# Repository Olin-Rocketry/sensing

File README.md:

# Sensing

Repository for all Olin Rocketry hardware and firmware.

The purpose of the avionics system is to determine when to deploy the drogue and main chutes, and to send the signal to do so to the recovery system. The flight computer contains several sensors to help detect apogee, and a microcontroller to read and process the data and send the signal.

The avionics system consists of

- a commercial-off-the-shelf (COTS) flight computer;
- a student-designed flight computer, which includes sensors, microcontroller, GPS, and radio; and
- a student-designed battery management system (BMS).

The COTS computer is a **\_** model. It has its own batteries, sensors, and radio and can trigger the recovery system independently. It is intended as a backup and is required by IREC competition rules (partly so they have a reliable altitude measurement for the competition). The BMS is described on the Power Management subteam page. It can suppy a steady 3.3V current up to about 1000 mA to the student-designed flight computer board.

**The flight computer consists of a Teensy 3.6 microcontroller and various sensors.**

- The [Teensy 3.6](https://www.pjrc.com/teensy/card9a_rev1.pdf) is computationally powerful enough for complex data processing, has many interrupt pins, and many pins in general for connecting multiple sensors. It also has a built-in SD card reader. The decision to use it was made before the Fall 2020 semester; other options were considered and may be viable for future iterations. The main drawback of the Teensy 3.6 is its cost, at around $30. This makes having multiple prototypes very expensive, especially if we want to distribute copies to team members living in separate places.
- We considered 3 different inertial measurement units (IMUs, or accelerometers):
  - [ADXL345](https://www.analog.com/media/en/technical-documentation/data-sheets/ADXL345.pdf) is a very common 3-axis accelerometer. It is widely available and was already in stock from JLC, the company manufacturing our board. This means our boards will have the ADXL345 already populated when it is shipped to us, a bonus.
  - [BMI088](https://download.mikroe.com/documents/datasheets/BMI088_Datasheet.pdf) is a 6-axis accelerometer and gyroscope (axes 4-6 are angular acceleration).
  - [BNO055](https://cdn-shop.adafruit.com/datasheets/BST_BNO055_DS000_12.pdf) is a 9-axis accelerometer, relative, and absolute gyroscope (axes 7-9 are absolute orientation).

We designed our Rev1 PCB to hold all three IMUs, so that we could test all of them at once. However, as of ordering time in January, the BMI088 and BNO055 were out of stock at Digikey and Mouser, so these were never tested.

- [MPL3115A2](https://www.nxp.com/docs/en/data-sheet/MPL3115A2.pdf) is a barometer calibrated to provide altimetry. It is the most important sensor, as it allows us to determine our absolute altitude. Our simplest apogee detection is triggered by a certain number of consecutive decreasing altitude measurements.
- Header pins for the [Adafruit Ultimate GPS Breakout (Version 3)](https://www.adafruit.com/product/746?__hstc), a $40 complete GPS module.
- Header pins for the [RFM9X LoRa Packet Radio Breakout](https://learn.adafruit.com/adafruit-rfm69hcw-and-rfm96-rfm95-rfm98-lora-packet-padio-breakouts/arduino-wiring), the currenty preferred radio (see Communications subteam page).

**Rev 1 Testing Update: Spring 2021**

The sensors on Rev1 (the ADXL345 accelerometer and the MPL3115A2 barometer) work, and the data can be read over I2C. The current data format is a csv file with time since launch, x, y, and z acceleration, pressure, altitude, and temperature. The readings from the accelerometer have very little noise when at rest (the only test performed so far - others to follow soon). The barometer has some issues. First of all, it has an offset of about 1.7 atmospheres. When those 1.7 atm are subtracted out, however, it provides high precision and sensitivity. The altitude readings are off by the same offset, as I believe they are calculated from the barometer reading anyway. The temperature has some 20 degrees F offset and significant drift of 2-5 degrees F over a few minutes. More testing to follow.

I looked at the specs and realized that the ADXL345 and MPL3115A2 together consume less than 3 mA of current at their max. Since the Teensy can output 250 mA through those pins, I don’t see why to use an external power source; we can just use the 3.3V pins on the Teensy.
The tests I have done have been using the 3.3V pin as a power source.

**Tests performed 3/26/2021:**

**Power supply test:** Get an external power supply and give 3.3V to the power inputs. Test the test points and the Teensy’s Vin pin. Test data logging onto SD card. Test sensors connected only to external power supply vs. connected to Teensy 3.3V pin vs. connected to both.

**Results:**
The transistor part of the Rev1 power management circuit did not work. For some reason, there was always only ~0.6V on both the gate and drain pins, and so 0.6V on the rest of the PCB. I tried several pin configurations and nothing helped. It worked fine when I bypassed the transistor and powered 3.3V to both the Teensy and the PCB.
The Teensy could not write to the SD card when the PCB and Teensy were powered independently; it only works when the rest of the PCB is powered through the Teensy’s dedicated 3.3V pin. Therefore, I recommend just using the Teensy’s 3.3V pin to power the sensors.

In this case, I suggest the voltage supplied by the BMS should be 3.6V instead of 3.3V, so that the linear voltage regulator on the Teensy can effectively supply the 3.3V to the sensors. Voltage regulators necessariy have a small voltage drop across them, although I came across a [source](https://forum.pjrc.com/threads/55789-Power-Teensy-3-6-with-lipo-battery?p=203568&viewfull=1#post203568) that says the Teensy will bypass its voltage regulator if the voltage is too low, so there is not necessarily an issue.

**MPL3115A2 Accuracy Test:** Take the Rev1 board up and down the stairs of the MAC building 2 times and measure altitude difference.

**Results:**
The readings are inaccurate, yet very precise. The pressure has reads on the order of 200 kPa, which is double what is expected (1 atmosphere is about 100 kPa), and the temperature reads 90 degrees F in a 70 degree room. Yet after the offset is subtracted, the sensor tracks changes in height of less than 20 feet (the distance between floors in the MAC, and the highest resolution analyzed) quite well. The graph below shows the corrected elevation and temperature over the course of my trip up and down the stairs of the MAC, then outside onto the great lawn and up to the 4th floor of West Hall. There is some drift over time as it sat on my desk after “landing,” on the order of 20 feet over 20 minutes. This is worrying, but it will likely not be a problem during a launch lasting a few minutes.

**Developing the Rev 2 board**

With the ADXL345 and MPL3115A2 sensors confirmed to work, the main objective of the Rev 2 board is to make it fit into the avionics bay. The final board is 80mm tall by 72mm wide and has a mounting hole in each corner. The power supply transistor circuit has been replaced with a power multiplexer, a zener diode was added for overvoltage protection, and the power from the BMS goes directly into the Vin pin on the Teensy; the sensors and other circuitry are powered by the Teensy's 3.3V pin as discussed above. Additionally, 5 debugging LEDs, one power LED, and a [buzzer](https://www.digikey.com/en/products/detail/mallory-sonalert-products-inc/PT-1340P-P10-PQ/4996070) have also been added and are controlled by spare digital pins on the Teensy. A 10uF capacitor was added between the power and ground pins of the radio upon testing by the Communications team.

The board has been ordered from JLC and will arrive within a couple days.

## Guide to creating PCBs

**The process for creating the flight computer PCB has multiple stages:**
  1. Components are selected, including the microcontroller and sensors.
  2. Schematics are created for each sensor individually. This mainly involves copying the circuit diagram from the datasheets for each sensor. Every sensor needs at least two capacitors for its power source, and some require external pull-up resistors, for example. The BNO055 is connected to an external crystal oscillator. It’s also a good idea to add test points (basically large, labelled vias) for debugging purposes. We tried to add a test point to every trace on the schematic that would not be directly connected to the microcontroller (because we can access those traces directly through the microcontroller’s pins). 
  3. For the Rev1 board, footprints for the BNO055 and MPL3115A2 were created by copying the dimensions given by the datasheets. The other footprints were downloaded from snapeda.com. In reality, the only reason to create them manually is to get practice with KiCAD, which is why it was done this way for two of the sensors; in future, snapeda.com likely has all the footprints we will need, without the possibility of human error.*
  4. At this stage, layouts are also created for the supporting circuitry surrounding each sensor individually. These layouts will be manually recreated later, but it is easier to go through a few iterations to find the optimal footprint placements now, before all the layouts are combined on one board.
  5. Now, all of the individual schematics are moved into one place. This can be done in the KiCAD schematic editor (eeschema) by clicking File -> Append Schematic Sheet Content -> then navigate to the schematic to import and click Use Relative Path.
  6. Now all the schematics can be hooked up together; in this case it means connecting each sensor’s communication pins to the Teensy and power and ground to the power supply. A small circuit for regulating the power supply from the BMS, as well as header pins for the BMS and GPS and radio breakout boards are also added to this schematic.
  7. Review the schematics with the flight computer sub-team. Hopefully we have been checking in all along, but now is the last chance to make changes before a lot of work goes into the layout. After this, even small changes to the schematic can be very hard to implement in the layout without starting over.
  8. The layout of all the components for the final PCB is created. You cannot copy and paste the layouts created earlier for individual sensors, but you can follow the prior layouts as a guide. For the Rev1 board, we kept the components in the same relative orientation but did not pack them as closely together, to make debugging and potential fixes easier. During the layout process, it will probably make sense to swap the order of some pins connected to the microcontroller, in order to untangle the traces, or reduce the number of times traces have to cross over. Most pins on the Teensy 3.6 can function in the same way, so switching which pins are connected to which sensor is not a problem. Be careful not to switch the order of SCK and SDA; MISO and MOSI; or RX and TX; these pins are not interchangeable.
  9. It's a good idea to add filled zones on the front and back of the board. Having filled zones helps reduce signal noise and is standard practice. It also means there are fewer traces you have to draw. I usually make my filled zones be ground on both sides of the PCB, with an abundance of vias throughout the board to connect the front and back ground planes. Remember to press 'B' to redraw the zones in KiCAD.
  10. When the layout is done and reviewed, it is sent to JLC, our manufacturer. JLC can populate the PCB with basic components like capacitors, resistors, and even the ADXL345. They did not have any of the other sensors in stock, so we will solder those on campus. We will also solder header pins and large components like the power-regulating MOSFET transistor (which will be discontinued in Rev2).
  11. Next up is writing the firmware to test the sensors and hopefully getting some data!

\* In fact, I did make a very significant error while copying the footprint from the datasheet for both the BNO055 and the MPL3115. I copied the pads as they were shown in the datasheet, which was a bottom-up view. What matters for the layout is the top-down view (think about how the sensor sits on the PCB; you want to design the pads so they sit directly beneath the sensor). When you design the pads using the bottom-up view, you get a mirror image of how they are supposed to be. Moreover, since the footprints are often symmetrical, it can be impossible to tell you’ve made a mistake, until you realize that the pins things are supposed to be connected to are actually on the opposite side of the chip.

### Rev2 images

**Rev2 full schematic**

**Rev2 power supply**

**Rev2 layout**

**Rev2 3D model (front)**

**Rev2 3D model (back)**

### Rev1 images

**Rev1 full schematic**

**Rev1 power supply**

**Rev1 layout**

**Rev1 3D model (front)**

**Rev1 3D model (back)**

## Ordering PCBs From JLCPCB

For ordering the boards, go to JLCPCB.com (https://jlcpcb.com/RAT), and click on "Quote Now" button.

JLCPCB (ShenzhenJLC Electronics Co., Ltd.), is the largest PCB prototype enterprise in China, and a high-tech manufacturer specializing in quick PCB prototype and small-batch PCB production. You can order a minimum of 5 PCBs for just $2.

First: Upload the gerber files for the board by clicking the "Add gerber file" button. You’ll notice a message at the bottom if the file is successfully uploaded.

A correctly uploaded gerber folder renders the board as follows:

Second: In order to get the board assembled (optional, based on the project requirements), select the "SMT Assembly option. It is important to select the side of the PCB that needs to be assembled, as well as the quantity for SMT. Press the "Confirm" button, then press the "Next" button.

Third: upload the BOM (Bill of Material) and CPL (Component Placement List) files and click the "Next" button. It is necessary to make sure that each of these files follow the jlcpcb specified BOM and CPL formats, respectively:

- [Sample BOM](https://jlcpcb.com//video/JLCSMT_Sample_BOM1.xlsx?_ga=2.42560357.1905056644.1612161700-100444678.1610257845)
- [Sample CPL](https://jlcpcb.com//video/JLCSMT_Sample_CPL1.xlsx?_ga=2.42560357.1905056644.1612161700-100444678.1610257845)
- [SMT FAQ's](https://support.jlcpcb.com/category/78-smt-assembly?_ga=2.42560357.1905056644.1612161700-100444678.1610257845)

Note: If there is an issue with the BOM/CPL formatting, the the page will keep erroring out until it is resolved.

Fourth: The parts are automatically detected through the uploaded BOM. They are also matched against jlcpcb's in-stock parts. It is important to go through each row and confirm if the auto-detected parts are the desired parts. Some parts will remain undetected if they cannot be assembled through SMT and require manual assembly post-deilvery.

Fifth: The website renders an assembled board using the CPL file. This feature can be used to review the placement of the components (including orientation). Once carefull reviewed, the next step is to download a list of parts remaining to be assembled towards the bottom of this page view. It is important to place an order for the remaining components to be manually assembled upon delivery.

Sixth: Click on the “Save to Cart” button. Then, click on the "Secure Checkout" button.

Last: Add the payment details and choose the suitable delivery method (this includes FedEx, DHL, and standard mail options). Then, place the order.

Optional: To review the production status of the board, click on the "Order History" button under username. Then, click on In Production > view progress to obtain timestamps for each of the production steps in real time.

**Design Reviews**

-November 11, 2022 6:00 PM (done)

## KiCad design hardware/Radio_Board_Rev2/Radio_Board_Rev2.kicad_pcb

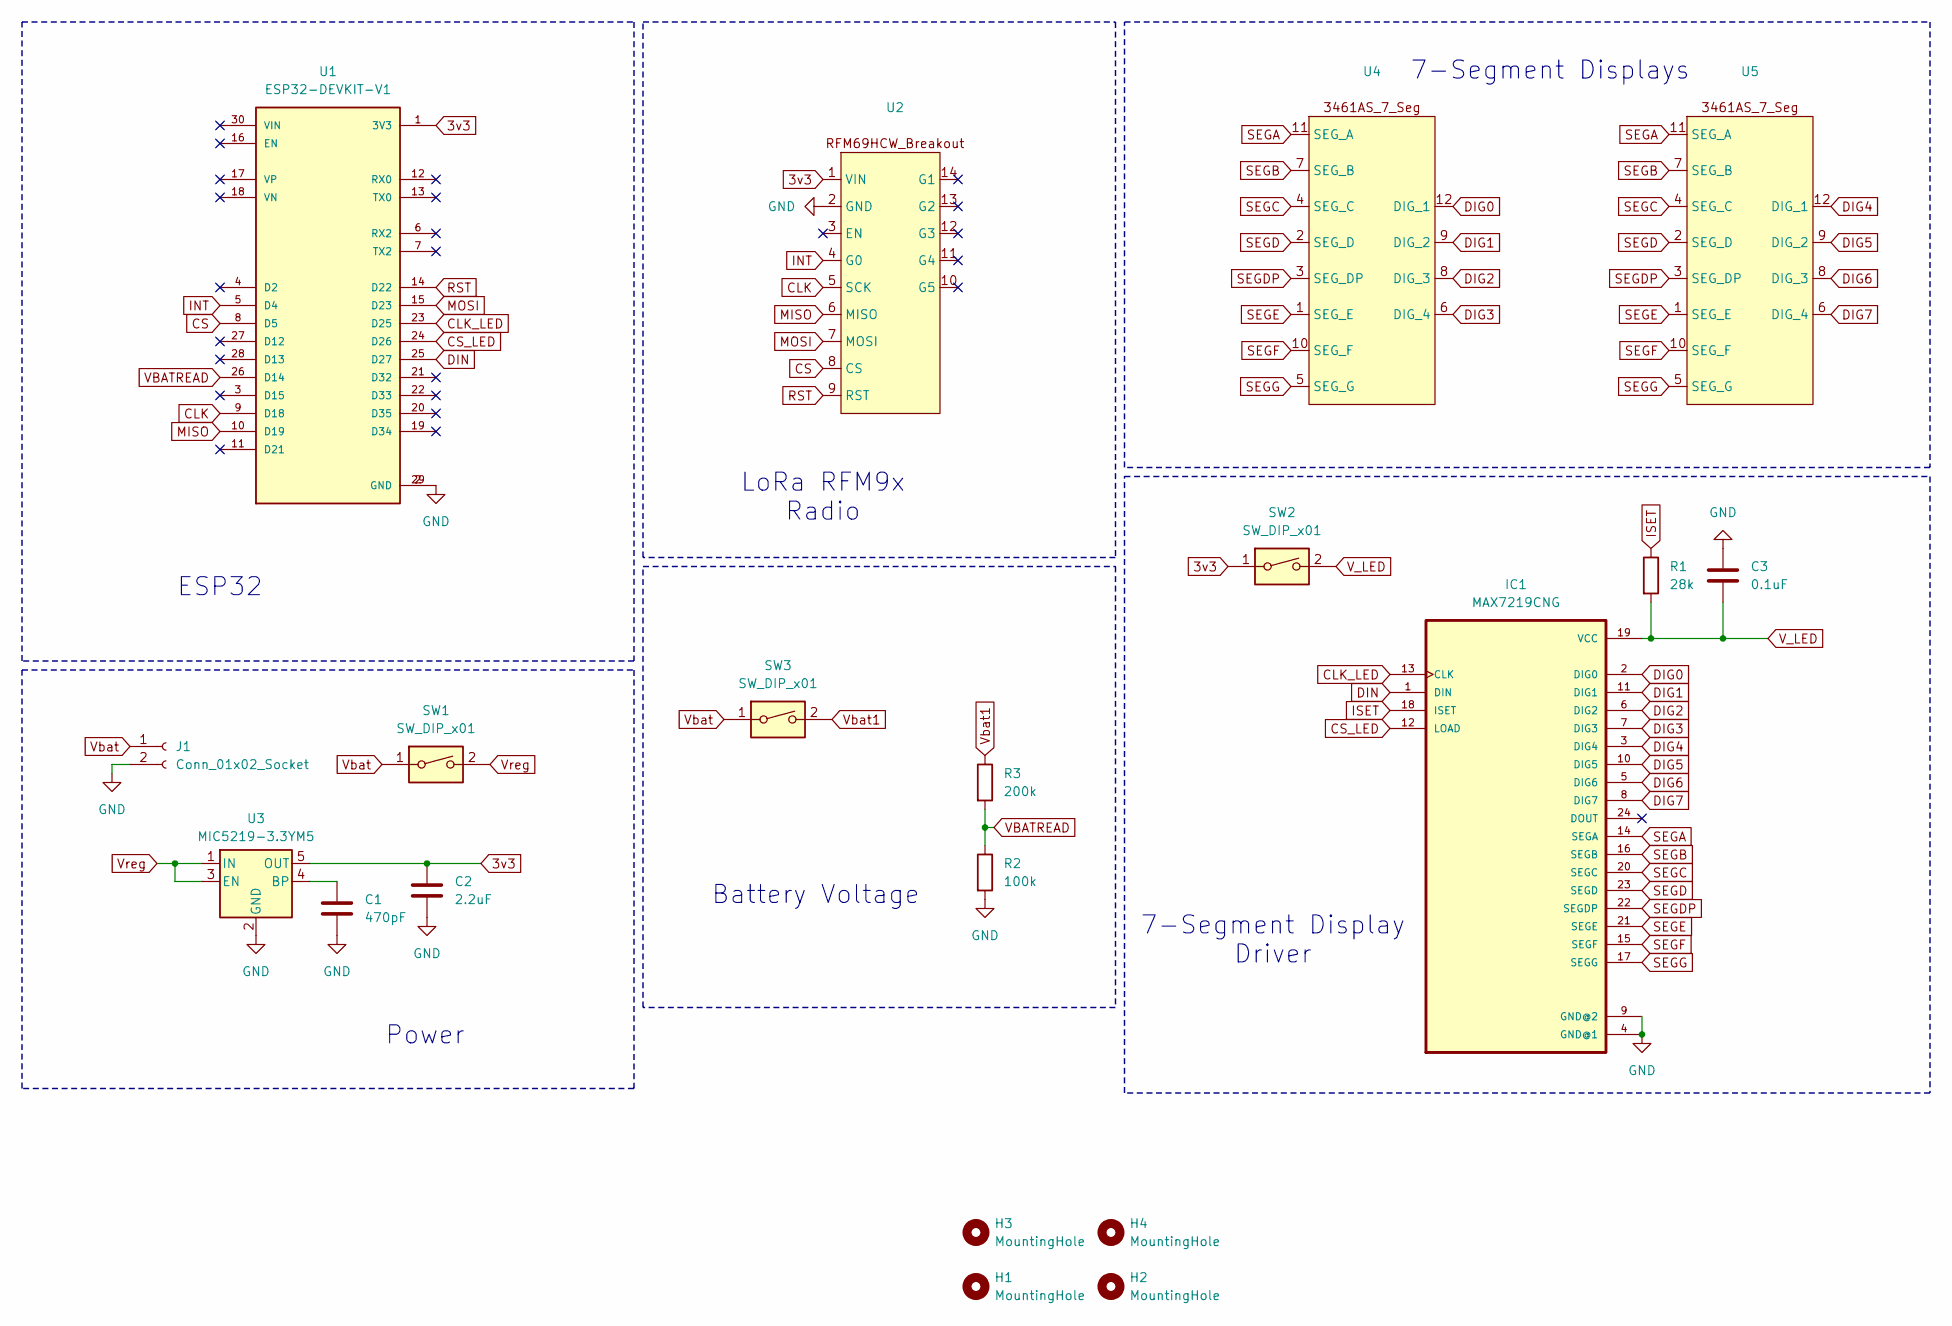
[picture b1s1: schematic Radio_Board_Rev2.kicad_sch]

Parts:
C1: 470pF; C_0603_1608Metric_Pad1.08x0.95mm_HandSolder
C2: 2.2uF; C_0603_1608Metric_Pad1.08x0.95mm_HandSolder
C3: 0.1uF; C_0603_1608Metric_Pad1.08x0.95mm_HandSolder
H1, H2, H3, H4: MountingHole; MountingHole_3.2mm_M3_DIN965_Pad_TopBottom
IC1: MAX7219CNG; DIP794W47P254L3213H457Q24
J1: Conn_01x02_Socket; JST_XH_B2B-XH-A_1x02_P2.50mm_Vertical
R1: 28k; R_0603_1608Metric_Pad0.98x0.95mm_HandSolder
R2: 100k; R_0603_1608Metric_Pad0.98x0.95mm_HandSolder
R3: 200k; R_0603_1608Metric_Pad0.98x0.95mm_HandSolder
SW1, SW2, SW3: SW_DIP_x01; PinSocket_1x02_P2.54mm_Vertical
U1: ESP32-DEVKIT-V1; MODULE_ESP32_DEVKIT_V1; PARTREV N/A
U2: RFM69HCW_Breakout
U3: MIC5219-3.3YM5; SOT-23-5
U4, U5: 3461AS_7_seg

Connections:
3v3: C2.1, SW2.1, U1.1 (3V3), U2.1 (VIN), U3.5 (OUT)
CLK: U1.9 (D18), U2.5 (SCK)
CLK_LED: IC1.13 (CLK), U1.23 (D25)
CS: U1.8 (D5), U2.8 (CS)
CS_LED: IC1.12 (LOAD), U1.24 (D26)
DIG0: IC1.2 (DIG0), U4.12 (DIG_1); also elsewhere on the board
DIG1: IC1.11 (DIG1), U4.9 (DIG_2); also elsewhere on the board
DIG2: IC1.6 (DIG2), U4.8 (DIG_3); also elsewhere on the board
DIG3: IC1.7 (DIG3), U4.6 (DIG_4); also elsewhere on the board
DIG4: IC1.3 (DIG4), U5.12 (DIG_1); also elsewhere on the board
DIG5: IC1.10 (DIG5), U5.9 (DIG_2); also elsewhere on the board
DIG6: IC1.5 (DIG6), U5.8 (DIG_3); also elsewhere on the board
DIG7: IC1.8 (DIG7), U5.6 (DIG_4); also elsewhere on the board
DIN: IC1.1 (DIN), U1.25 (D27)
GND: C1.2, C2.2, C3.1, IC1.4 (GND@1), IC1.9 (GND@2), J1.2, R2.2, U1.2 (GND), U1.29 (GND), U2.2 (GND), U3.2 (GND)
INT: U1.5 (D4), U2.4 (G0)
ISET: IC1.18 (ISET), R1.1
MISO: U1.10 (D19), U2.6 (MISO)
MOSI: U1.15 (D23), U2.7 (MOSI)
unnamed: C1.1, U3.4 (BP)
RST: U1.14 (D22), U2.9 (RST)
SEGA: IC1.14 (SEGA), U4.11 (SEG_A), U5.11 (SEG_A); also elsewhere on the board
SEGB: IC1.16 (SEGB), U4.7 (SEG_B), U5.7 (SEG_B); also elsewhere on the board
SEGC: IC1.20 (SEGC), U4.4 (SEG_C), U5.4 (SEG_C); also elsewhere on the board
SEGD: IC1.23 (SEGD), U4.2 (SEG_D), U5.2 (SEG_D); also elsewhere on the board
SEGDP: IC1.22 (SEGDP), U4.3 (SEG_DP), U5.3 (SEG_DP); also elsewhere on the board
SEGE: IC1.21 (SEGE), U4.1 (SEG_E), U5.1 (SEG_E); also elsewhere on the board
SEGF: IC1.15 (SEGF), U4.10 (SEG_F), U5.10 (SEG_F); also elsewhere on the board
SEGG: IC1.17 (SEGG), U4.5 (SEG_G), U5.5 (SEG_G); also elsewhere on the board
VBATREAD: R2.1, R3.2, U1.26 (D14)
V_LED: C3.2, IC1.19 (VCC), R1.2, SW2.2
Vbat: J1.1, SW1.1, SW3.1
Vbat1: R3.1, SW3.2
Vreg: SW1.2, U3.1 (IN), U3.3 (EN)

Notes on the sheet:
Battery Voltage
Power
ESP32
7-Segment Display Driver
7-Segment Displays
LoRa RFM9x Radio

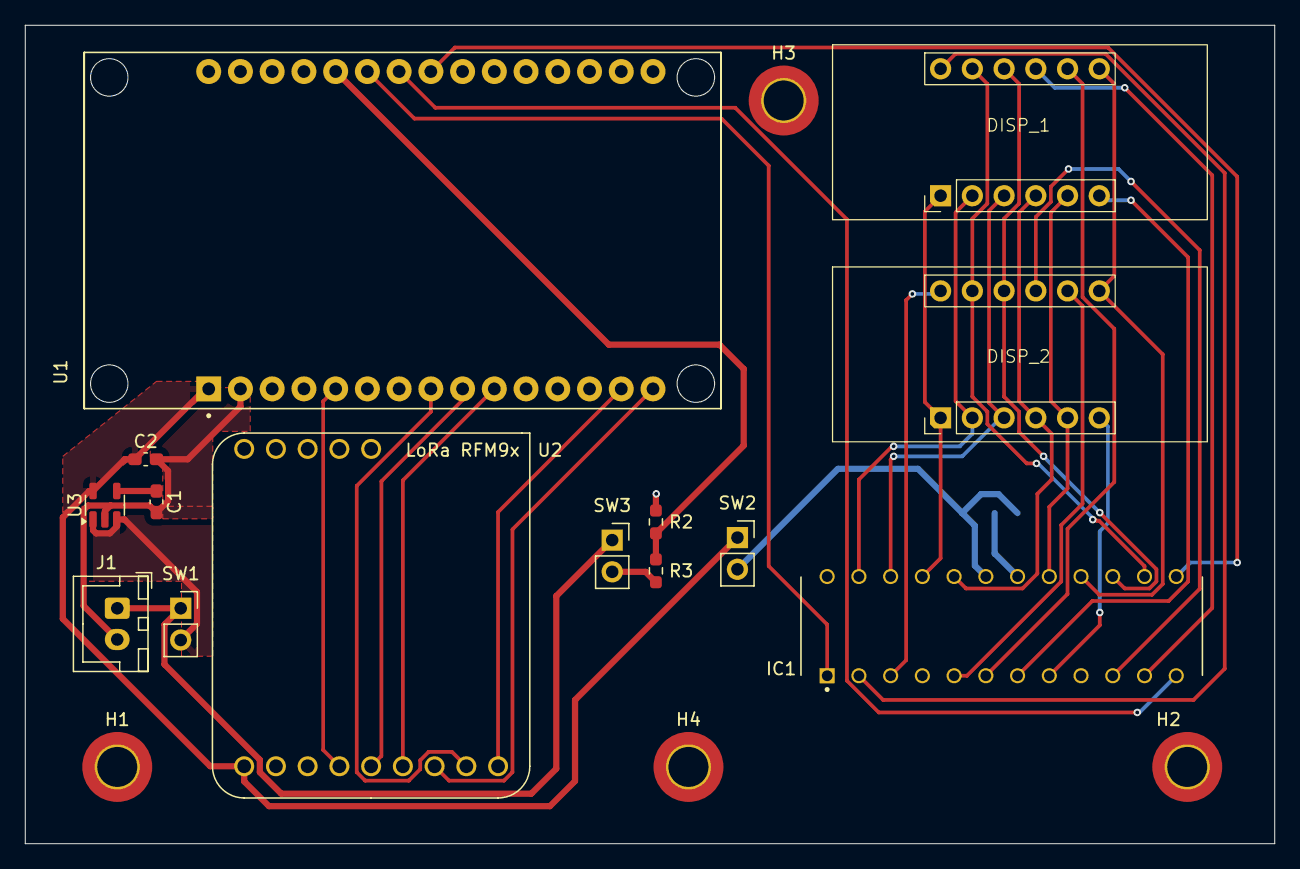
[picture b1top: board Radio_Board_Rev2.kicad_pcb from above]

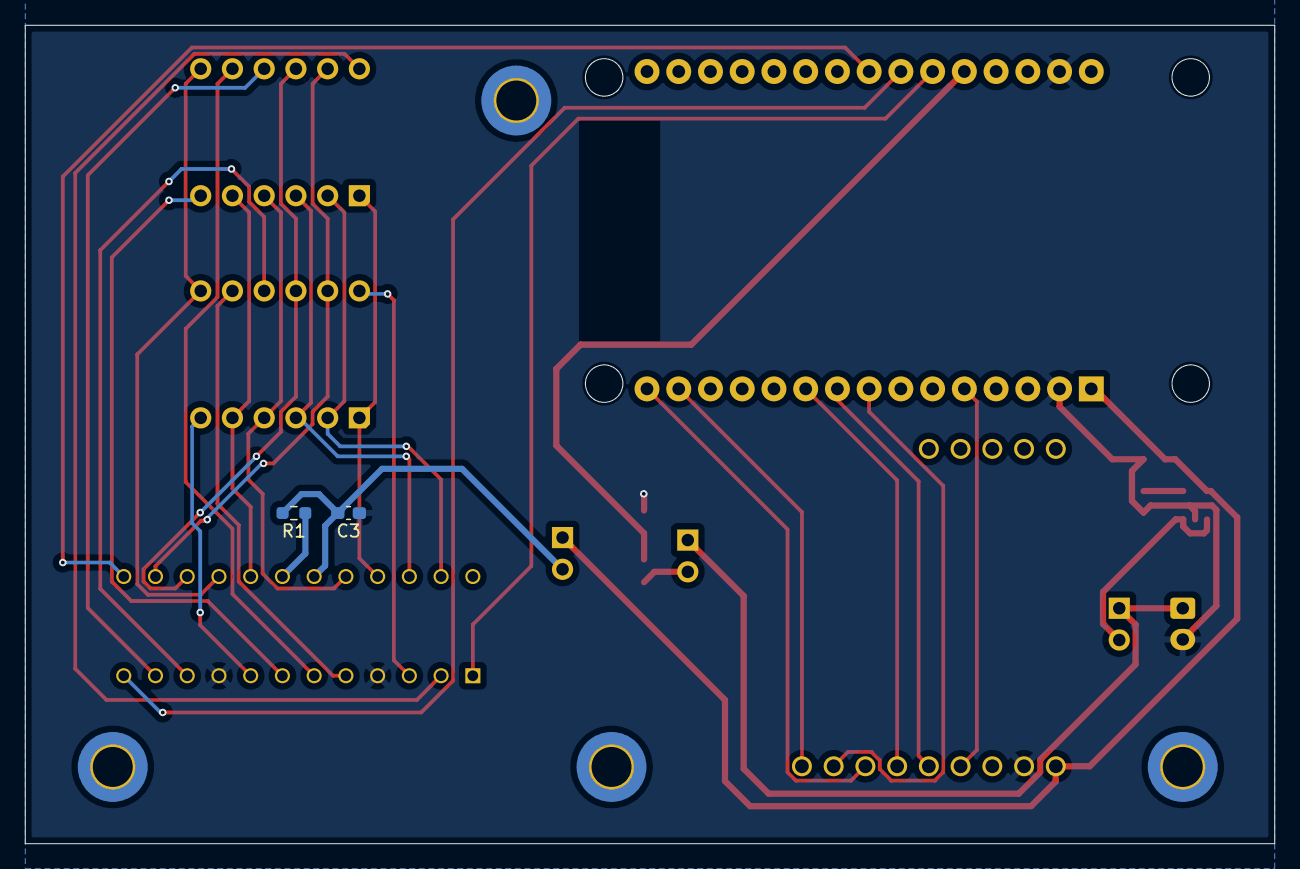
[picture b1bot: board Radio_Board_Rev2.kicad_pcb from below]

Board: 2 copper layers, 100.0 x 65.5 mm, 20 parts (2 on the bottom side), 34 nets.

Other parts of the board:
DISP_1, DISP_2: 3461AS_7_seg

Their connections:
DIG0: DISP_1.12 (DIG_1); also elsewhere on the board
DIG1: DISP_1.9 (DIG_2); also elsewhere on the board
DIG2: DISP_1.8 (DIG_3); also elsewhere on the board
DIG3: DISP_1.6 (DIG_4); also elsewhere on the board
DIG4: DISP_2.12 (DIG_1); also elsewhere on the board
DIG5: DISP_2.9 (DIG_2); also elsewhere on the board
DIG6: DISP_2.8 (DIG_3); also elsewhere on the board
DIG7: DISP_2.6 (DIG_4); also elsewhere on the board
SEGA: DISP_1.11 (SEG_A), DISP_2.11 (SEG_A); also elsewhere on the board
SEGB: DISP_1.7 (SEG_B), DISP_2.7 (SEG_B); also elsewhere on the board
SEGC: DISP_1.4 (SEG_C), DISP_2.4 (SEG_C); also elsewhere on the board
SEGD: DISP_1.2 (SEG_D), DISP_2.2 (SEG_D); also elsewhere on the board
SEGDP: DISP_1.3 (SEG_DP), DISP_2.3 (SEG_DP); also elsewhere on the board
SEGE: DISP_1.1 (SEG_E), DISP_2.1 (SEG_E); also elsewhere on the board
SEGF: DISP_1.10 (SEG_F), DISP_2.10 (SEG_F); also elsewhere on the board
SEGG: DISP_1.5 (SEG_G), DISP_2.5 (SEG_G); also elsewhere on the board

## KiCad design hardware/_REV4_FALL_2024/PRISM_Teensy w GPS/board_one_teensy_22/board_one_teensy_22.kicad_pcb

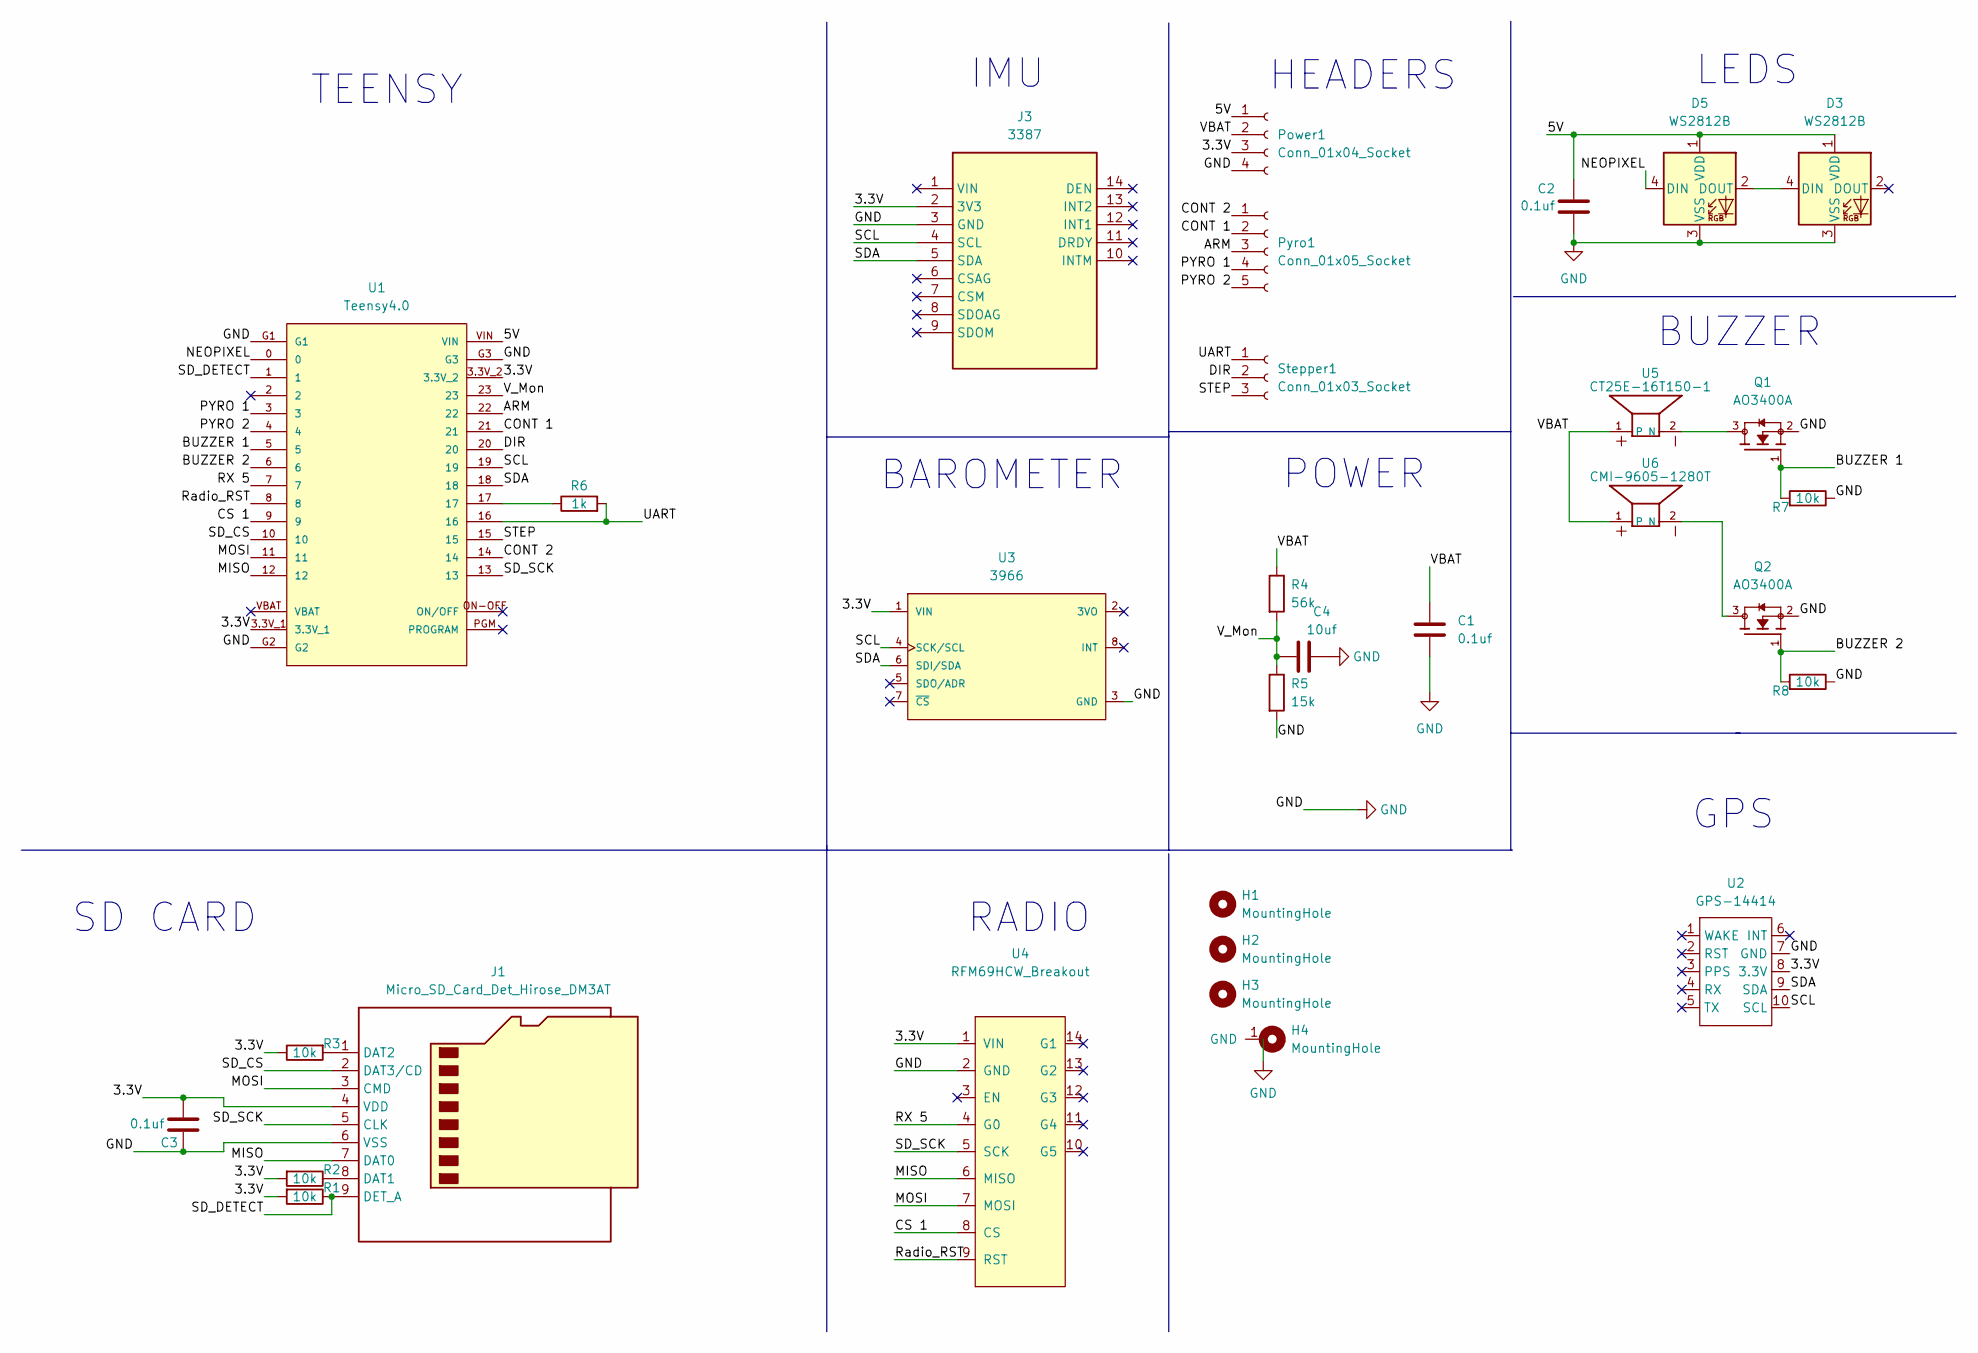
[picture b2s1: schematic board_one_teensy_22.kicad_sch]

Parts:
C1, C2, C3: 0.1uf; C_0603_1608Metric_Pad1.08x0.95mm_HandSolder
C4: 10uf; C_0603_1608Metric
D3, D5: WS2812B
H1, H2, H3, H4: MountingHole; MountingHole_3.2mm_M3_DIN965_Pad_TopBottom
J1: Micro_SD_Card_Det_Hirose_DM3AT; HRS_DM3CS-SF
J3: 3387; IMU MIni; Manufacturer_Part_Number 3387
Power1: Conn_01x04_Socket; PinHeader_1x04_P2.54mm_Vertical
Pyro1: Conn_01x05_Socket; PinHeader_1x05_P2.54mm_Vertical
Q1, Q2: AO3400A; SOT95P280X125-3N; PARTREV L
R1, R2, R3, R7, R8: 10k; R_0603_1608Metric_Pad0.98x0.95mm_HandSolder
R4: 56k; R_0603_1608Metric_Pad0.98x0.95mm_HandSolder
R5: 15k; R_0603_1608Metric_Pad0.98x0.95mm_HandSolder
R6: 1k; R_0603_1608Metric_Pad0.98x0.95mm_HandSolder
Stepper1: Conn_01x03_Socket; PinHeader_1x03_P2.54mm_Vertical
U1: Teensy4.0; MODULE_DEV-15583
U2: GPS-14414
U3: 3966; Adafruit_Industries-3966-MFG; mouser part number 485-3966; digikey description BMP388 - PRECISION BAROMETRIC PR
U4: RFM69HCW_Breakout
U5: CT25E-16T150-1; PARTREV 31/03/20
U6: CMI-9605-1280T; PARTREV 31/03/20

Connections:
/3.3V: C3.2, J1.4 (VDD), J3.2 (3V3), Power1.3, R1.2, R2.2, R3.1, U1.3.3V_1, U1.3.3V_2, U2.8 (3.3V), U3.1 (VIN), U4.1 (VIN)
/5V: C2.2, D3.1 (VDD), D5.1 (VDD), Power1.1, U1.VIN
/ARM: Pyro1.3, U1.22
/BUZZER 1: Q1.1, R7.2, U1.5
/BUZZER 2: Q2.1, R8.2, U1.6
/CONT 1: Pyro1.2, U1.21
/CONT 2: Pyro1.1, U1.14
/CS 1: U1.9, U4.8 (CS)
/DIR: Stepper1.2, U1.20
/MISO: J1.7 (DAT0), U1.12, U4.6 (MISO)
/MOSI: J1.3 (CMD), U1.11, U4.7 (MOSI)
/NEOPIXEL: D5.4 (DIN), U1.0
/PYRO 1: Pyro1.4, U1.3
/PYRO 2: Pyro1.5, U1.4
/RX 5: U1.7, U4.4 (G0)
/Radio_RST: U1.8, U4.9 (RST)
/SCL: J3.4 (SCL), U1.19, U2.10 (SCL), U3.4 (SCK/SCL)
/SDA: J3.5 (SDA), U1.18, U2.9 (SDA), U3.6 (SDI/SDA)
/SD_CS: J1.2 (DAT3/CD), U1.10
/SD_DETECT: J1.9 (DET_A), R1.1, U1.1
/SD_SCK: J1.5 (CLK), U1.13, U4.5 (SCK)
/STEP: Stepper1.3, U1.15
/UART: R6.2, Stepper1.1, U1.16
/VBAT: C1.1, Power1.2, R4.1, U5.1, U6.1
/V_Mon: C4.2, R4.2, R5.1, U1.23
GND: C1.2, C2.1, C3.1, C4.1, D3.3 (VSS), D5.3 (VSS), H4.1 (GND), J1.6 (VSS), J3.3 (GND), Power1.4, Q1.2, Q2.2, R5.2, R7.1, R8.1, U1.G1, U1.G2, U1.G3, U2.7 (GND), U3.3 (GND), U4.2 (GND)
unnamed: D3.4 (DIN), D5.2 (DOUT)
unnamed: J1.8 (DAT1), R2.1
unnamed: J1.1 (DAT2), R3.2
unnamed: R6.1, U1.17
unnamed: Q1.3, U5.2 (N)
unnamed: Q2.3, U6.2 (N)

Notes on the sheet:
BUZZER
TEENSY
HEADERS
SD CARD
POWER
LEDS
GPS
IMU
BAROMETER
RADIO

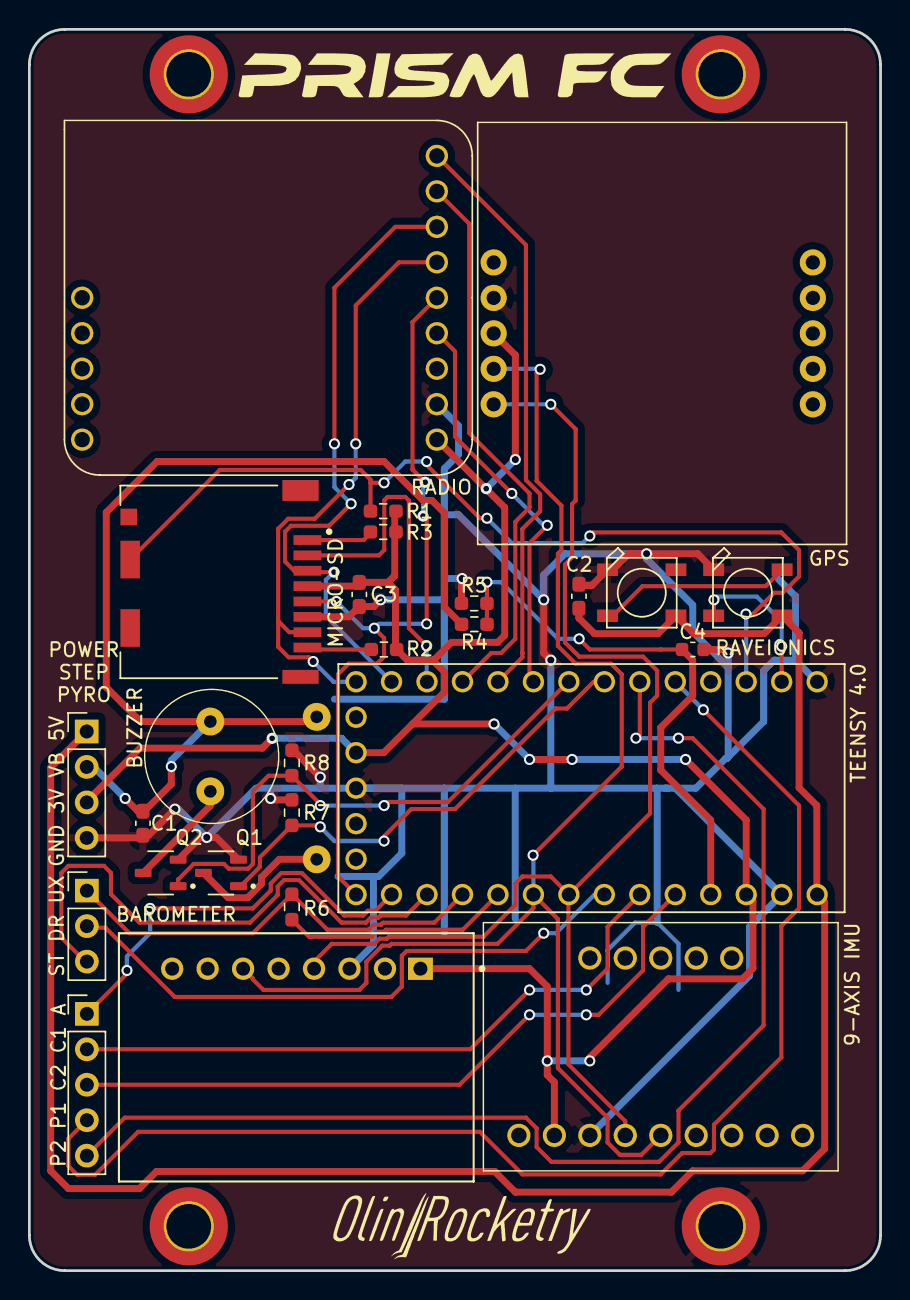
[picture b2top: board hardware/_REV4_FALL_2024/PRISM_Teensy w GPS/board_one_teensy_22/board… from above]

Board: 2 copper layers, 61.0 x 88.9 mm, 31 parts (1 on the bottom side), 32 nets.

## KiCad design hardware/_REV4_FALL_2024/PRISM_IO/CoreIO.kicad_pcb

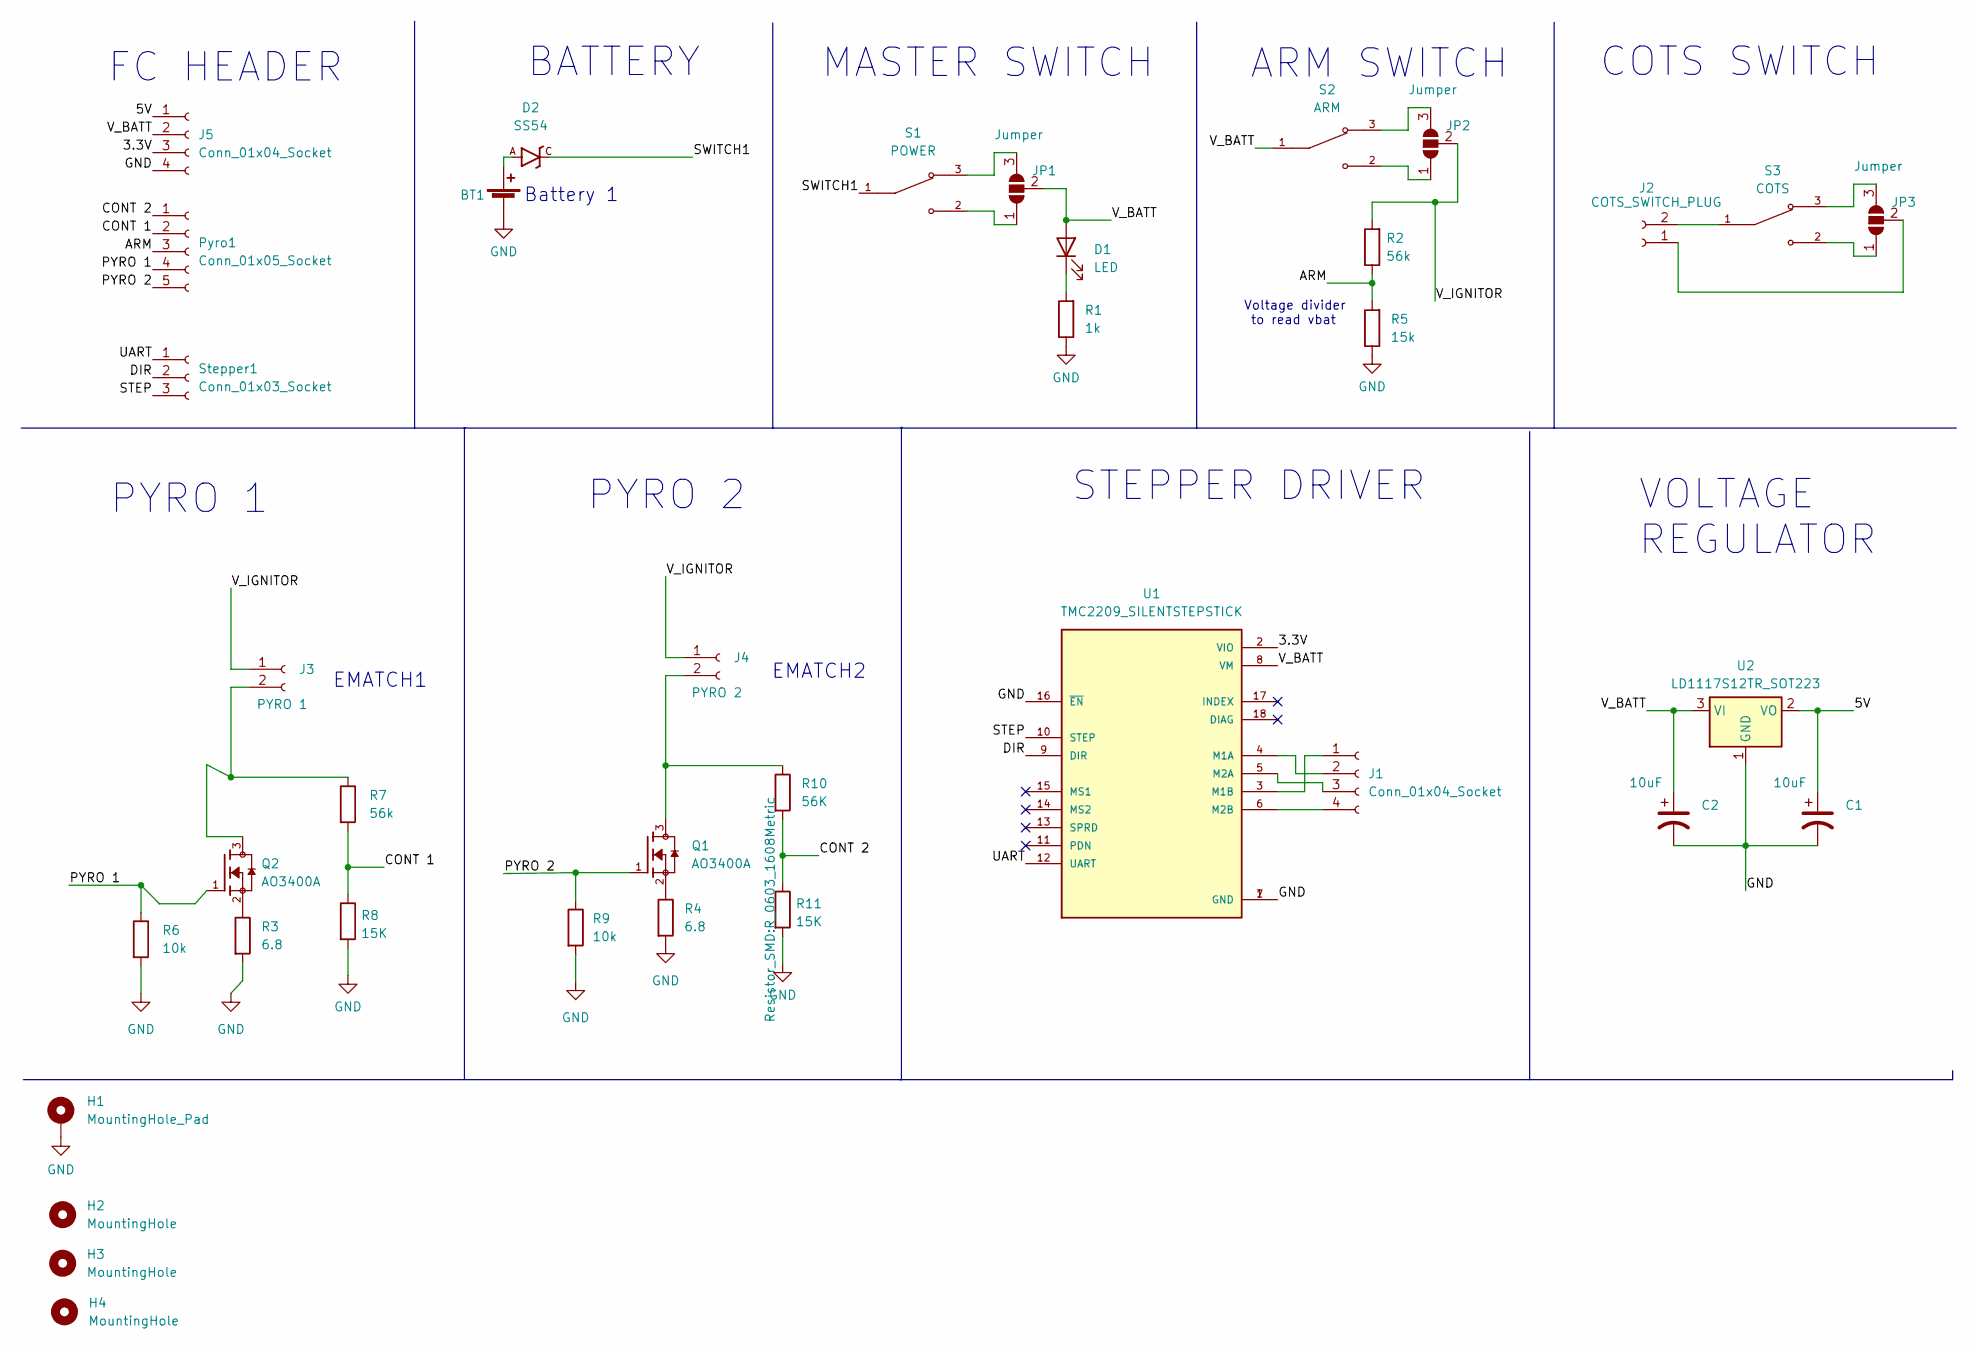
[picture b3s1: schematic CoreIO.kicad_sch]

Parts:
BT1: JST_XH_S02B-XH-A_02x2.50mm_Angled
C1, C2: 10uF; CP_EIA-3216-18_Kemet-A
D1: LED; LED_0603_1608Metric
D2: SS54; DO-214AC
H1: MountingHole_Pad; MountingHole_3.2mm_M3_DIN965_Pad_TopBottom
H2, H3, H4: MountingHole; MountingHole_3.2mm_M3_DIN965_Pad_TopBottom
J1: Conn_01x04_Socket; JST_XH_S04B-XH-A_04x2.50mm_Angled
J2: COTS_SWITCH_PLUG; JST_XH_S02B-XH-A_02x2.50mm_Angled
J3: PYRO 1; JST_XH_S02B-XH-A_02x2.50mm_Angled
J4: PYRO 2; JST_XH_S02B-XH-A_02x2.50mm_Angled
J5: Conn_01x04_Socket; PinHeader_1x04_P2.54mm_Vertical
JP1, JP2, JP3: Jumper; SolderJumper-3_P1.3mm_Open_Pad1.0x1.5mm_NumberLabels
Pyro1: Conn_01x05_Socket; PinHeader_1x05_P2.54mm_Vertical
Q1, Q2: AO3400A; SOT95P280X125-3N; PARTREV L
R1: 1k; R_0603_1608Metric
R2, R7: 56k; R_0603_1608Metric
R3, R4: 6.8; R_Axial_DIN0414_L11.9mm_D4.5mm_P15.24mm_Horizontal
R5: 15k; R_0603_1608Metric
R6, R9: 10k; R_0603_1608Metric
R8, R11: 15K; R_0603_1608Metric
R10: 56K; R_0603_1608Metric
S1: POWER; SW_D2F-01F; PARTREV B036-E1-12
S2: ARM; SW_D2F-01F; PARTREV B036-E1-12
S3: COTS; SW_D2F-01F; PARTREV B036-E1-12
Stepper1: Conn_01x03_Socket; PinHeader_1x03_P2.54mm_Vertical
U1: TMC2209_SILENTSTEPSTICK; MODULE_TMC2209_SILENTSTEPSTICK; PARTREV 1.20
U2: LD1117S12TR_SOT223; SOT-223-3_TabPin2

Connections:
/3.3V: J5.3, U1.2 (VIO)
/5V: C1.1, J5.1, U2.2 (VO)
/ARM: R2.1, R5.2; also elsewhere on the board
/CONT 1: R7.2, R8.1; also elsewhere on the board
/CONT 2: R10.2, R11.1; also elsewhere on the board
/DIR: U1.9 (DIR); also elsewhere on the board
/PYRO 1: Q2.1, R6.1; also elsewhere on the board
/PYRO 2: Q1.1, R9.1; also elsewhere on the board
/STEP: U1.10 (STEP); also elsewhere on the board
/SWITCH1: D2.C, S1.1
/UART: U1.12 (UART); also elsewhere on the board
/V_BATT: C2.1, D1.2 (A), J5.2, JP1.2 (C), S2.1, U1.8 (VM), U2.3 (VI)
/V_IGNITOR: J3.1, J4.1, JP2.2 (C), R2.2
GND: BT1.2 (-), C1.2, C2.2, H1.1, J5.4, R1.1, R3.2, R4.2, R5.1, R6.2, R8.2, R9.2, R11.2, U1.1 (GND), U1.7 (GND), U1.16 (~EN), U2.1 (GND)
unnamed: BT1.1 (+), D2.A
unnamed: D1.1 (K), R1.2
unnamed: J1.1, U1.3 (M1B)
unnamed: J1.2, U1.4 (M1A)
unnamed: J1.3, U1.5 (M2A)
unnamed: J1.4, U1.6 (M2B)
unnamed: J2.1, JP3.2 (C)
unnamed: J2.2, S3.1
unnamed: J3.2, Q2.3, R7.1
unnamed: J4.2, Q1.3, R10.1
unnamed: JP1.1 (A), S1.2
unnamed: JP1.3 (B), S1.3
unnamed: JP2.1 (A), S2.2
unnamed: JP2.3 (B), S2.3
unnamed: JP3.1 (A), S3.2
unnamed: JP3.3 (B), S3.3
unnamed: Q1.2, R4.1
unnamed: Q2.2, R3.1

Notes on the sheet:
ARM SWITCH
EMATCH1
PYRO 1
BATTERY
EMATCH2
Voltage divider to read vbat
VOLTAGE REGULATOR
MASTER SWITCH
PYRO 2
FC HEADER
STEPPER DRIVER
COTS SWITCH
Battery 1
